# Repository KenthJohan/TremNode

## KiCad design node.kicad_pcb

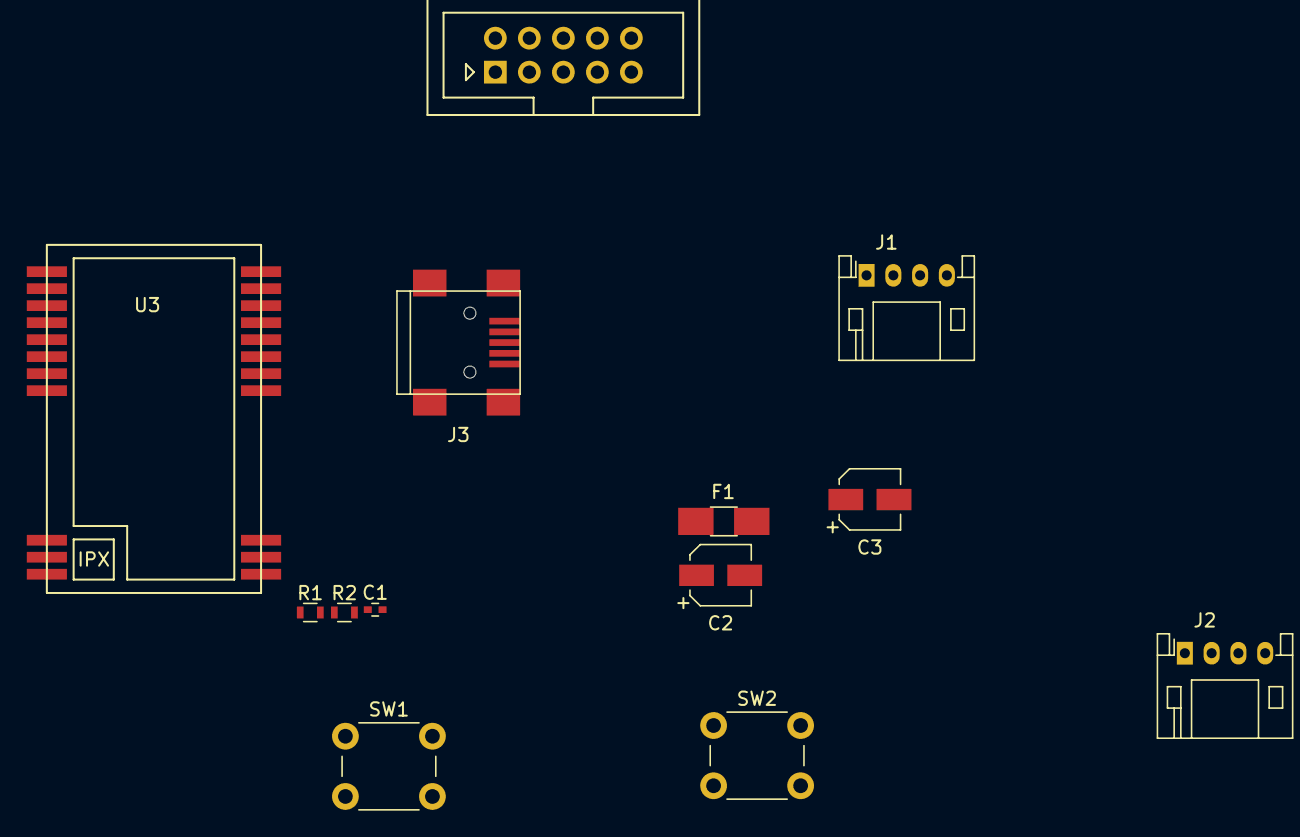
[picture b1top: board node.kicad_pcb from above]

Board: 2 copper layers, 13 parts (0 on the bottom side), 6 nets, no tracks yet.

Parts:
C1: 100nF; C_0402
C2, C3: CP; CP_Elec_4x4.5
F1: Fuse; Fuse_SMD1206_HandSoldering
J1, J2: Conn_01x04_Male; JST_PH_S4B-PH-K_04x2.00mm_Angled
J3: USB_B_Mini; USB_Mini-B
J4: Conn_02x05_Odd_Even; Multicomp_MC9A12-1034_2x05x2.54mm_Straight
R1: 10K; R_0603
R2: 220; R_0603
SW1, SW2: SW_Push; SW_PUSH_6mm
U3: CDSENET_E22-900M22S

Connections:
+3V3: C3.1, SW2.1
+5V: C2.1, F1.1, J1.3, J2.3, J4.1, R2.1
BOOT: R1.1, SW2.2
GND: C1.2, C2.2, C3.2, J1.4, J2.4, J3.5, J3.6, J4.3, J4.5, J4.9, R1.2, SW1.1
NRST: C1.1, J4.10, SW1.2
unnamed: F1.2, J3.1

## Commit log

2018-08-27 init
2018-10-24 hello
